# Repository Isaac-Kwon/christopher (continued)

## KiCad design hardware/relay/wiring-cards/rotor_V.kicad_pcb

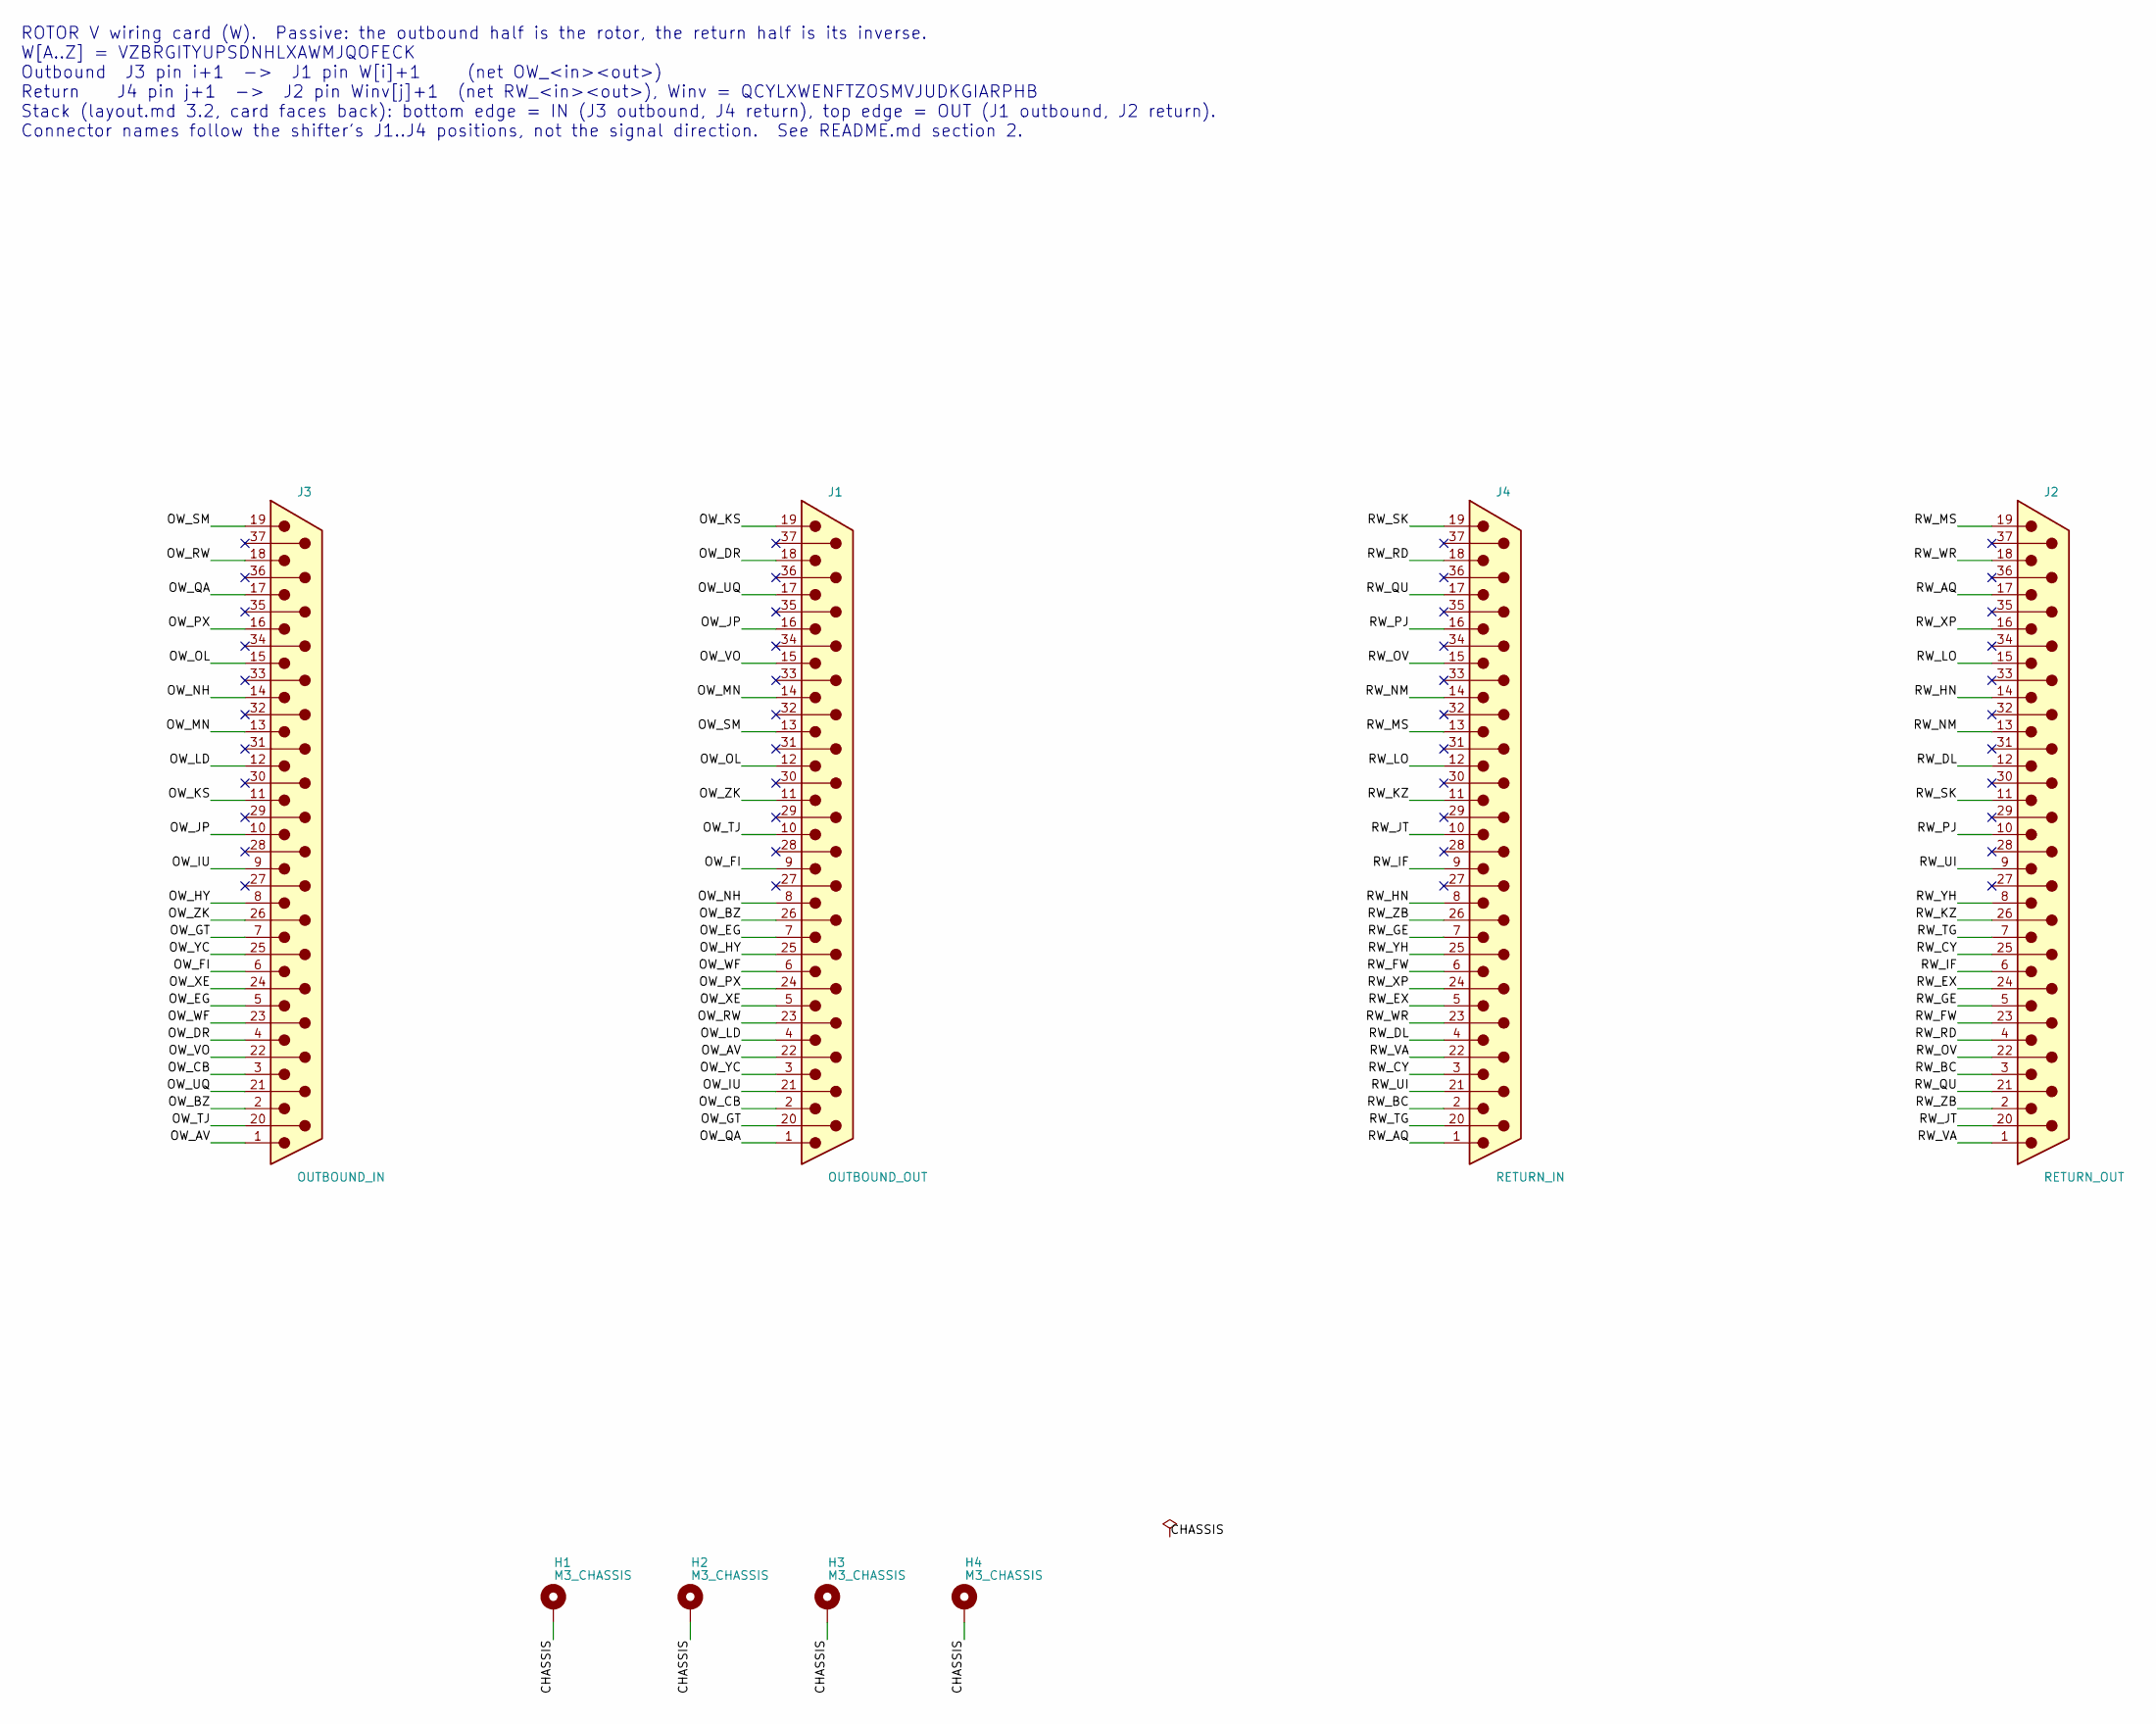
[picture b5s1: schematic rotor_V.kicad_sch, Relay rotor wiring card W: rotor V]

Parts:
H1, H2, H3, H4: M3_CHASSIS; MountingHole_3.2mm_M3_Pad
J1: OUTBOUND_OUT; DSUB-37_Pins_Horizontal_P2.77x2.84mm_EdgePinOffset9.90mm_Ho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
J2: RETURN_OUT; DSUB-37_Pins_Horizontal_P2.77x2.84mm_EdgePinOffset9.90mm_Ho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
J3: OUTBOUND_IN; DSUB-37_Pins_Horizontal_P2.77x2.84mm_EdgePinOffset9.90mm_Ho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
J4: RETURN_IN; DSUB-37_Pins_Horizontal_P2.77x2.84mm_EdgePinOffset9.90mm_Ho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

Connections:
/CHASSIS: H1.1, H2.1, H3.1, H4.1, J1.SH, J2.SH, J3.SH, J4.SH
/OW_AV: J1.22, J3.1
/OW_BZ: J1.26, J3.2
/OW_CB: J1.2, J3.3
/OW_DR: J1.18, J3.4
/OW_EG: J1.7, J3.5
/OW_FI: J1.9, J3.6
/OW_GT: J1.20, J3.7
/OW_HY: J1.25, J3.8
/OW_IU: J1.21, J3.9
/OW_JP: J1.16, J3.10
/OW_KS: J1.19, J3.11
/OW_LD: J1.4, J3.12
/OW_MN: J1.14, J3.13
/OW_NH: J1.8, J3.14
/OW_OL: J1.12, J3.15
/OW_PX: J1.24, J3.16
/OW_QA: J1.1, J3.17
/OW_RW: J1.23, J3.18
/OW_SM: J1.13, J3.19
/OW_TJ: J1.10, J3.20
/OW_UQ: J1.17, J3.21
/OW_VO: J1.15, J3.22
/OW_WF: J1.6, J3.23
/OW_XE: J1.5, J3.24
/OW_YC: J1.3, J3.25
/OW_ZK: J1.11, J3.26
/RW_AQ: J2.17, J4.1
/RW_BC: J2.3, J4.2
/RW_CY: J2.25, J4.3
/RW_DL: J2.12, J4.4
/RW_EX: J2.24, J4.5
/RW_FW: J2.23, J4.6
/RW_GE: J2.5, J4.7
/RW_HN: J2.14, J4.8
/RW_IF: J2.6, J4.9
/RW_JT: J2.20, J4.10
/RW_KZ: J2.26, J4.11
/RW_LO: J2.15, J4.12
/RW_MS: J2.19, J4.13
/RW_NM: J2.13, J4.14
/RW_OV: J2.22, J4.15
/RW_PJ: J2.10, J4.16
/RW_QU: J2.21, J4.17
/RW_RD: J2.4, J4.18
/RW_SK: J2.11, J4.19
/RW_TG: J2.7, J4.20
/RW_UI: J2.9, J4.21
/RW_VA: J2.1, J4.22
/RW_WR: J2.18, J4.23
/RW_XP: J2.16, J4.24
/RW_YH: J2.8, J4.25
/RW_ZB: J2.2, J4.26

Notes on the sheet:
ROTOR V wiring card (W). Passive: the outbound half is the rotor, the return half is its inverse. W[A..Z] = VZBRGITYUPSDNHLXAWMJQOFECK Outbound J3 pin i+1 -> J1 pin W[i]+1 (net OW_<in><out>) Return J4 pin j+1 -> J2 pin Winv[j]+1 (net RW_<in><out>), Winv = QCYLXWENFTZOSMVJUDKGIARPHB Stack (layout.md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

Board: 2 copper layers, 8 parts (0 on the bottom side), 53 nets, no tracks yet.

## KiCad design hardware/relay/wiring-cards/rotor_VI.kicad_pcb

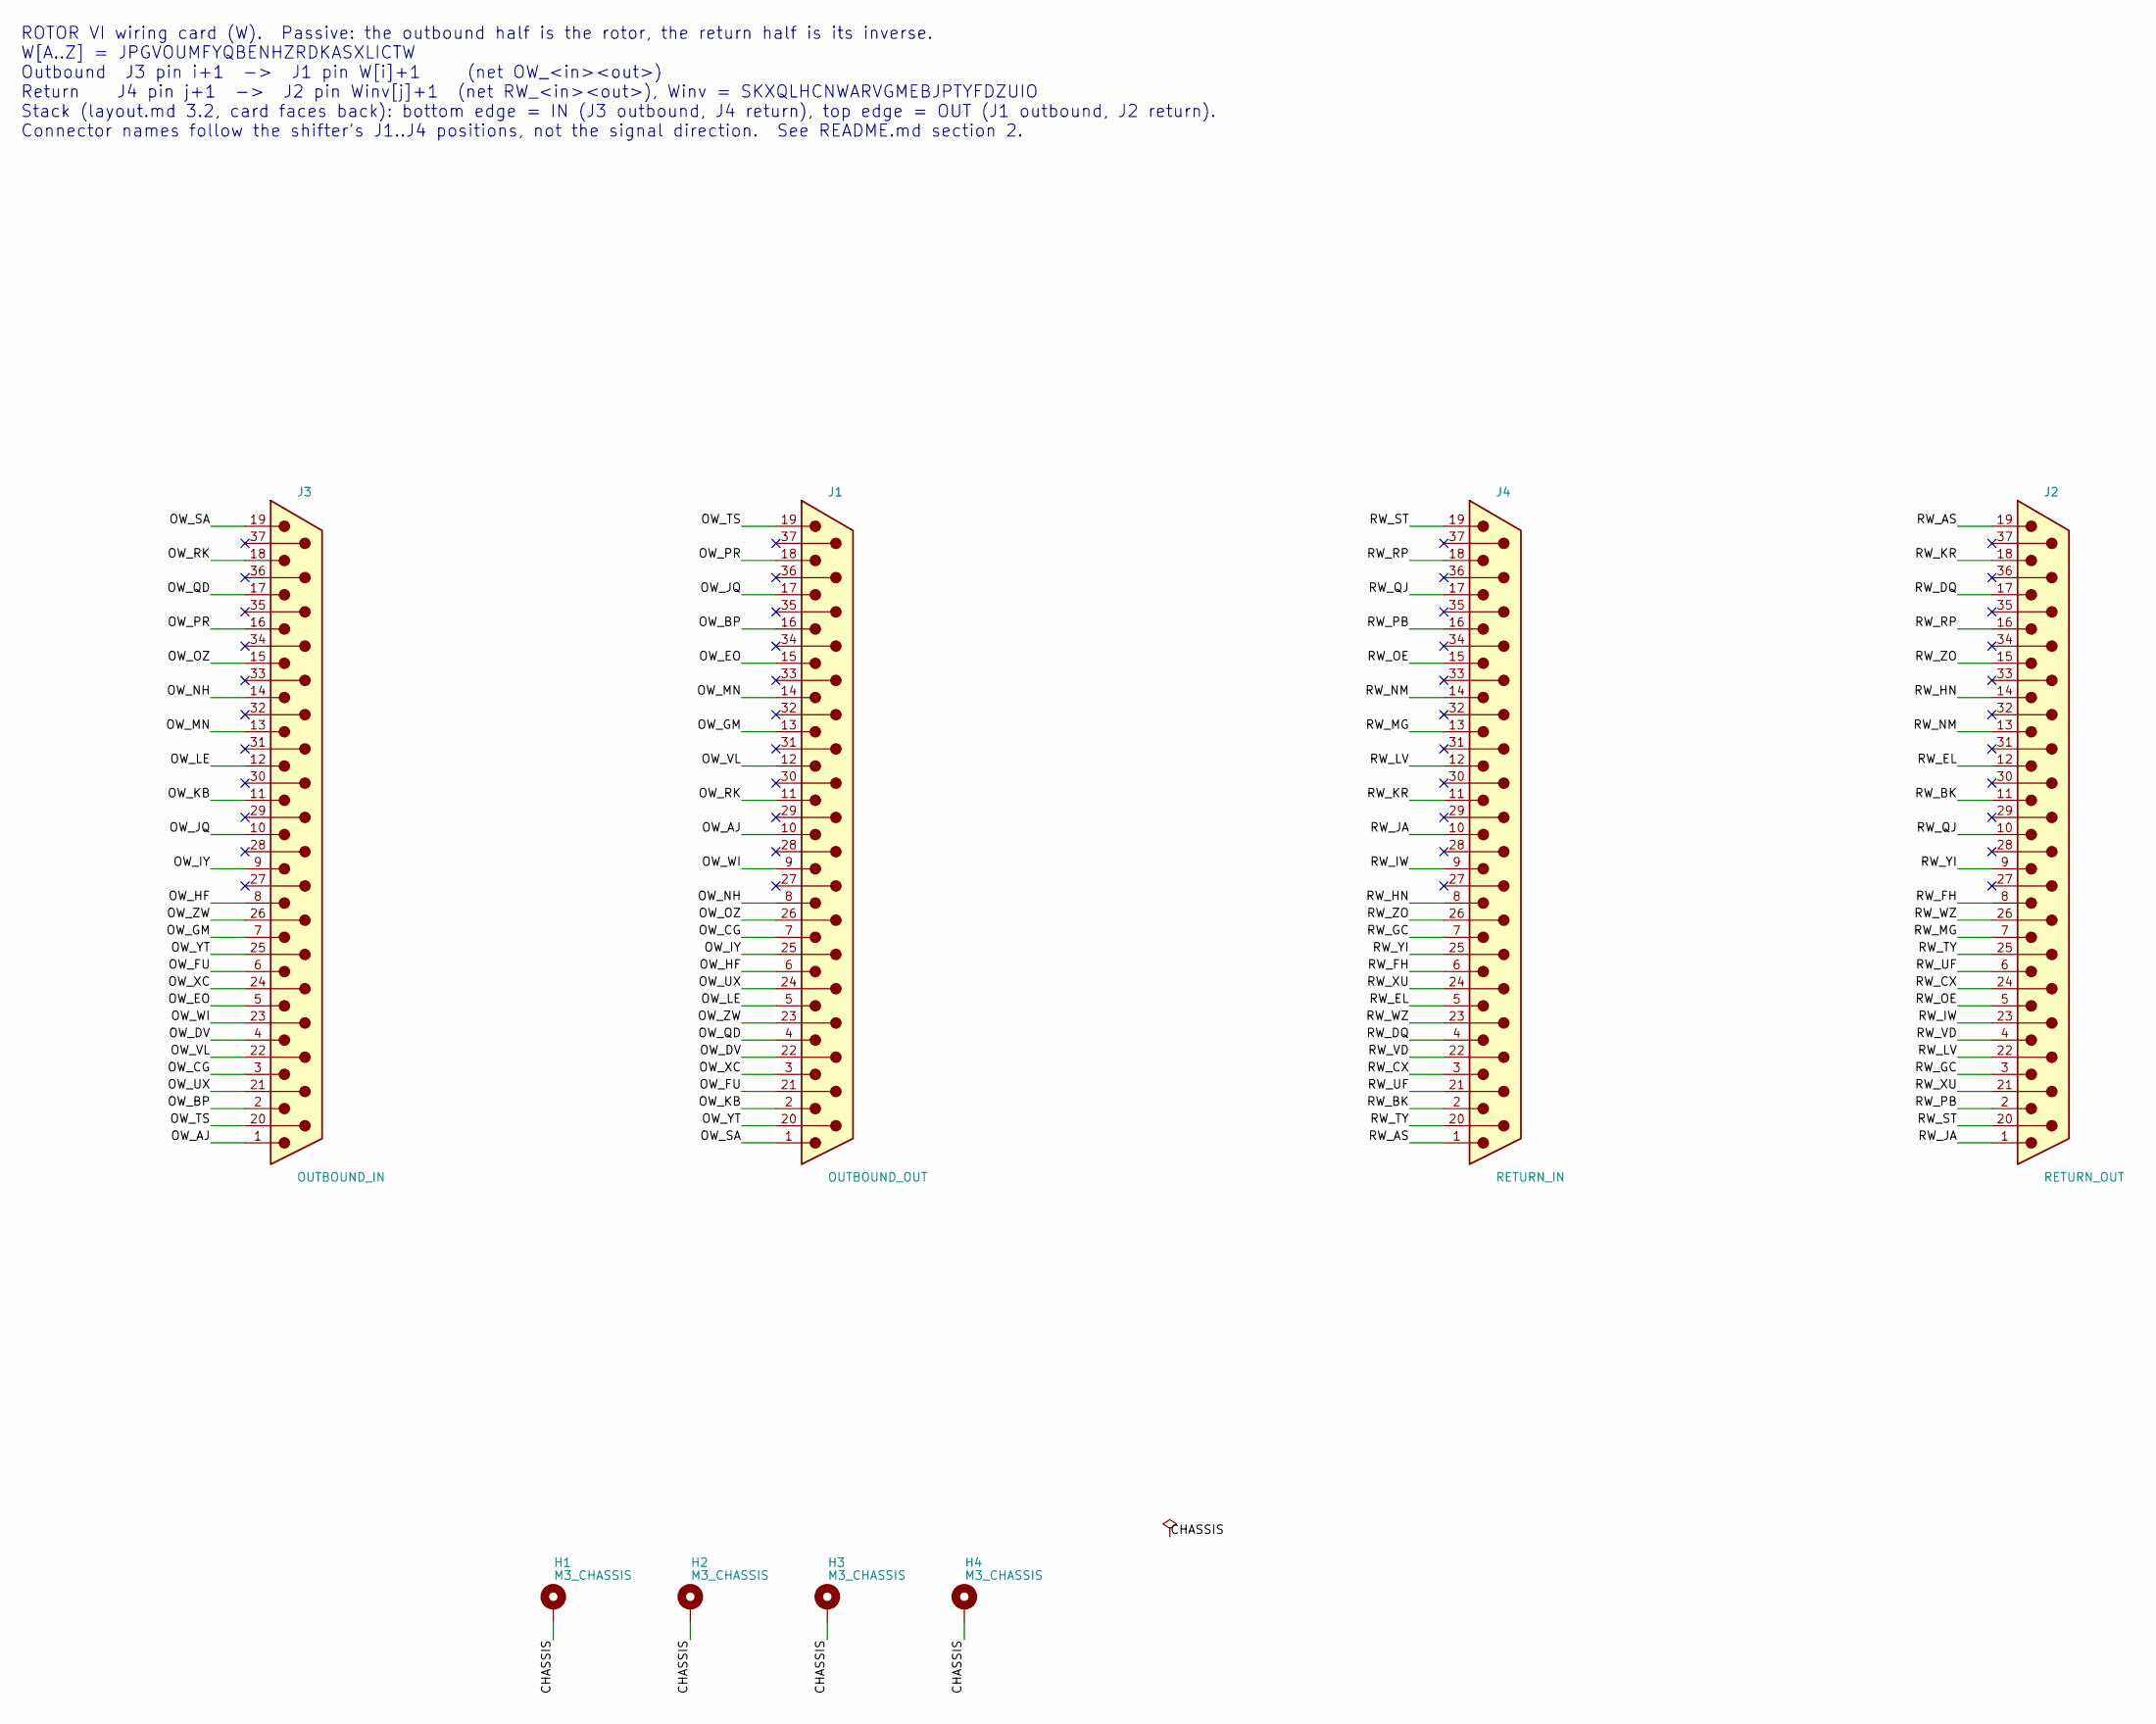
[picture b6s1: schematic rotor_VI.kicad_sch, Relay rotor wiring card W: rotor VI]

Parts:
H1, H2, H3, H4: M3_CHASSIS; MountingHole_3.2mm_M3_Pad
J1: OUTBOUND_OUT; DSUB-37_Pins_Horizontal_P2.77x2.84mm_EdgePinOffset9.90mm_Ho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
J2: RETURN_OUT; DSUB-37_Pins_Horizontal_P2.77x2.84mm_EdgePinOffset9.90mm_Ho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
J3: OUTBOUND_IN; DSUB-37_Pins_Horizontal_P2.77x2.84mm_EdgePinOffset9.90mm_Ho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
J4: RETURN_IN; DSUB-37_Pins_Horizontal_P2.77x2.84mm_EdgePinOffset9.90mm_Ho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

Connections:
/CHASSIS: H1.1, H2.1, H3.1, H4.1, J1.SH, J2.SH, J3.SH, J4.SH
/OW_AJ: J1.10, J3.1
/OW_BP: J1.16, J3.2
/OW_CG: J1.7, J3.3
/OW_DV: J1.22, J3.4
/OW_EO: J1.15, J3.5
/OW_FU: J1.21, J3.6
/OW_GM: J1.13, J3.7
/OW_HF: J1.6, J3.8
/OW_IY: J1.25, J3.9
/OW_JQ: J1.17, J3.10
/OW_KB: J1.2, J3.11
/OW_LE: J1.5, J3.12
/OW_MN: J1.14, J3.13
/OW_NH: J1.8, J3.14
/OW_OZ: J1.26, J3.15
/OW_PR: J1.18, J3.16
/OW_QD: J1.4, J3.17
/OW_RK: J1.11, J3.18
/OW_SA: J1.1, J3.19
/OW_TS: J1.19, J3.20
/OW_UX: J1.24, J3.21
/OW_VL: J1.12, J3.22
/OW_WI: J1.9, J3.23
/OW_XC: J1.3, J3.24
/OW_YT: J1.20, J3.25
/OW_ZW: J1.23, J3.26
/RW_AS: J2.19, J4.1
/RW_BK: J2.11, J4.2
/RW_CX: J2.24, J4.3
/RW_DQ: J2.17, J4.4
/RW_EL: J2.12, J4.5
/RW_FH: J2.8, J4.6
/RW_GC: J2.3, J4.7
/RW_HN: J2.14, J4.8
/RW_IW: J2.23, J4.9
/RW_JA: J2.1, J4.10
/RW_KR: J2.18, J4.11
/RW_LV: J2.22, J4.12
/RW_MG: J2.7, J4.13
/RW_NM: J2.13, J4.14
/RW_OE: J2.5, J4.15
/RW_PB: J2.2, J4.16
/RW_QJ: J2.10, J4.17
/RW_RP: J2.16, J4.18
/RW_ST: J2.20, J4.19
/RW_TY: J2.25, J4.20
/RW_UF: J2.6, J4.21
/RW_VD: J2.4, J4.22
/RW_WZ: J2.26, J4.23
/RW_XU: J2.21, J4.24
/RW_YI: J2.9, J4.25
/RW_ZO: J2.15, J4.26

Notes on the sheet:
ROTOR VI wiring card (W). Passive: the outbound half is the rotor, the return half is its inverse. W[A..Z] = JPGVOUMFYQBENHZRDKASXLICTW Outbound J3 pin i+1 -> J1 pin W[i]+1 (net OW_<in><out>) Return J4 pin j+1 -> J2 pin Winv[j]+1 (net RW_<in><out>), Winv = SKXQLHCNWARVGMEBJPTYFDZUIO Stack (layout.m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

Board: 2 copper layers, 8 parts (0 on the bottom side), 53 nets, no tracks yet.

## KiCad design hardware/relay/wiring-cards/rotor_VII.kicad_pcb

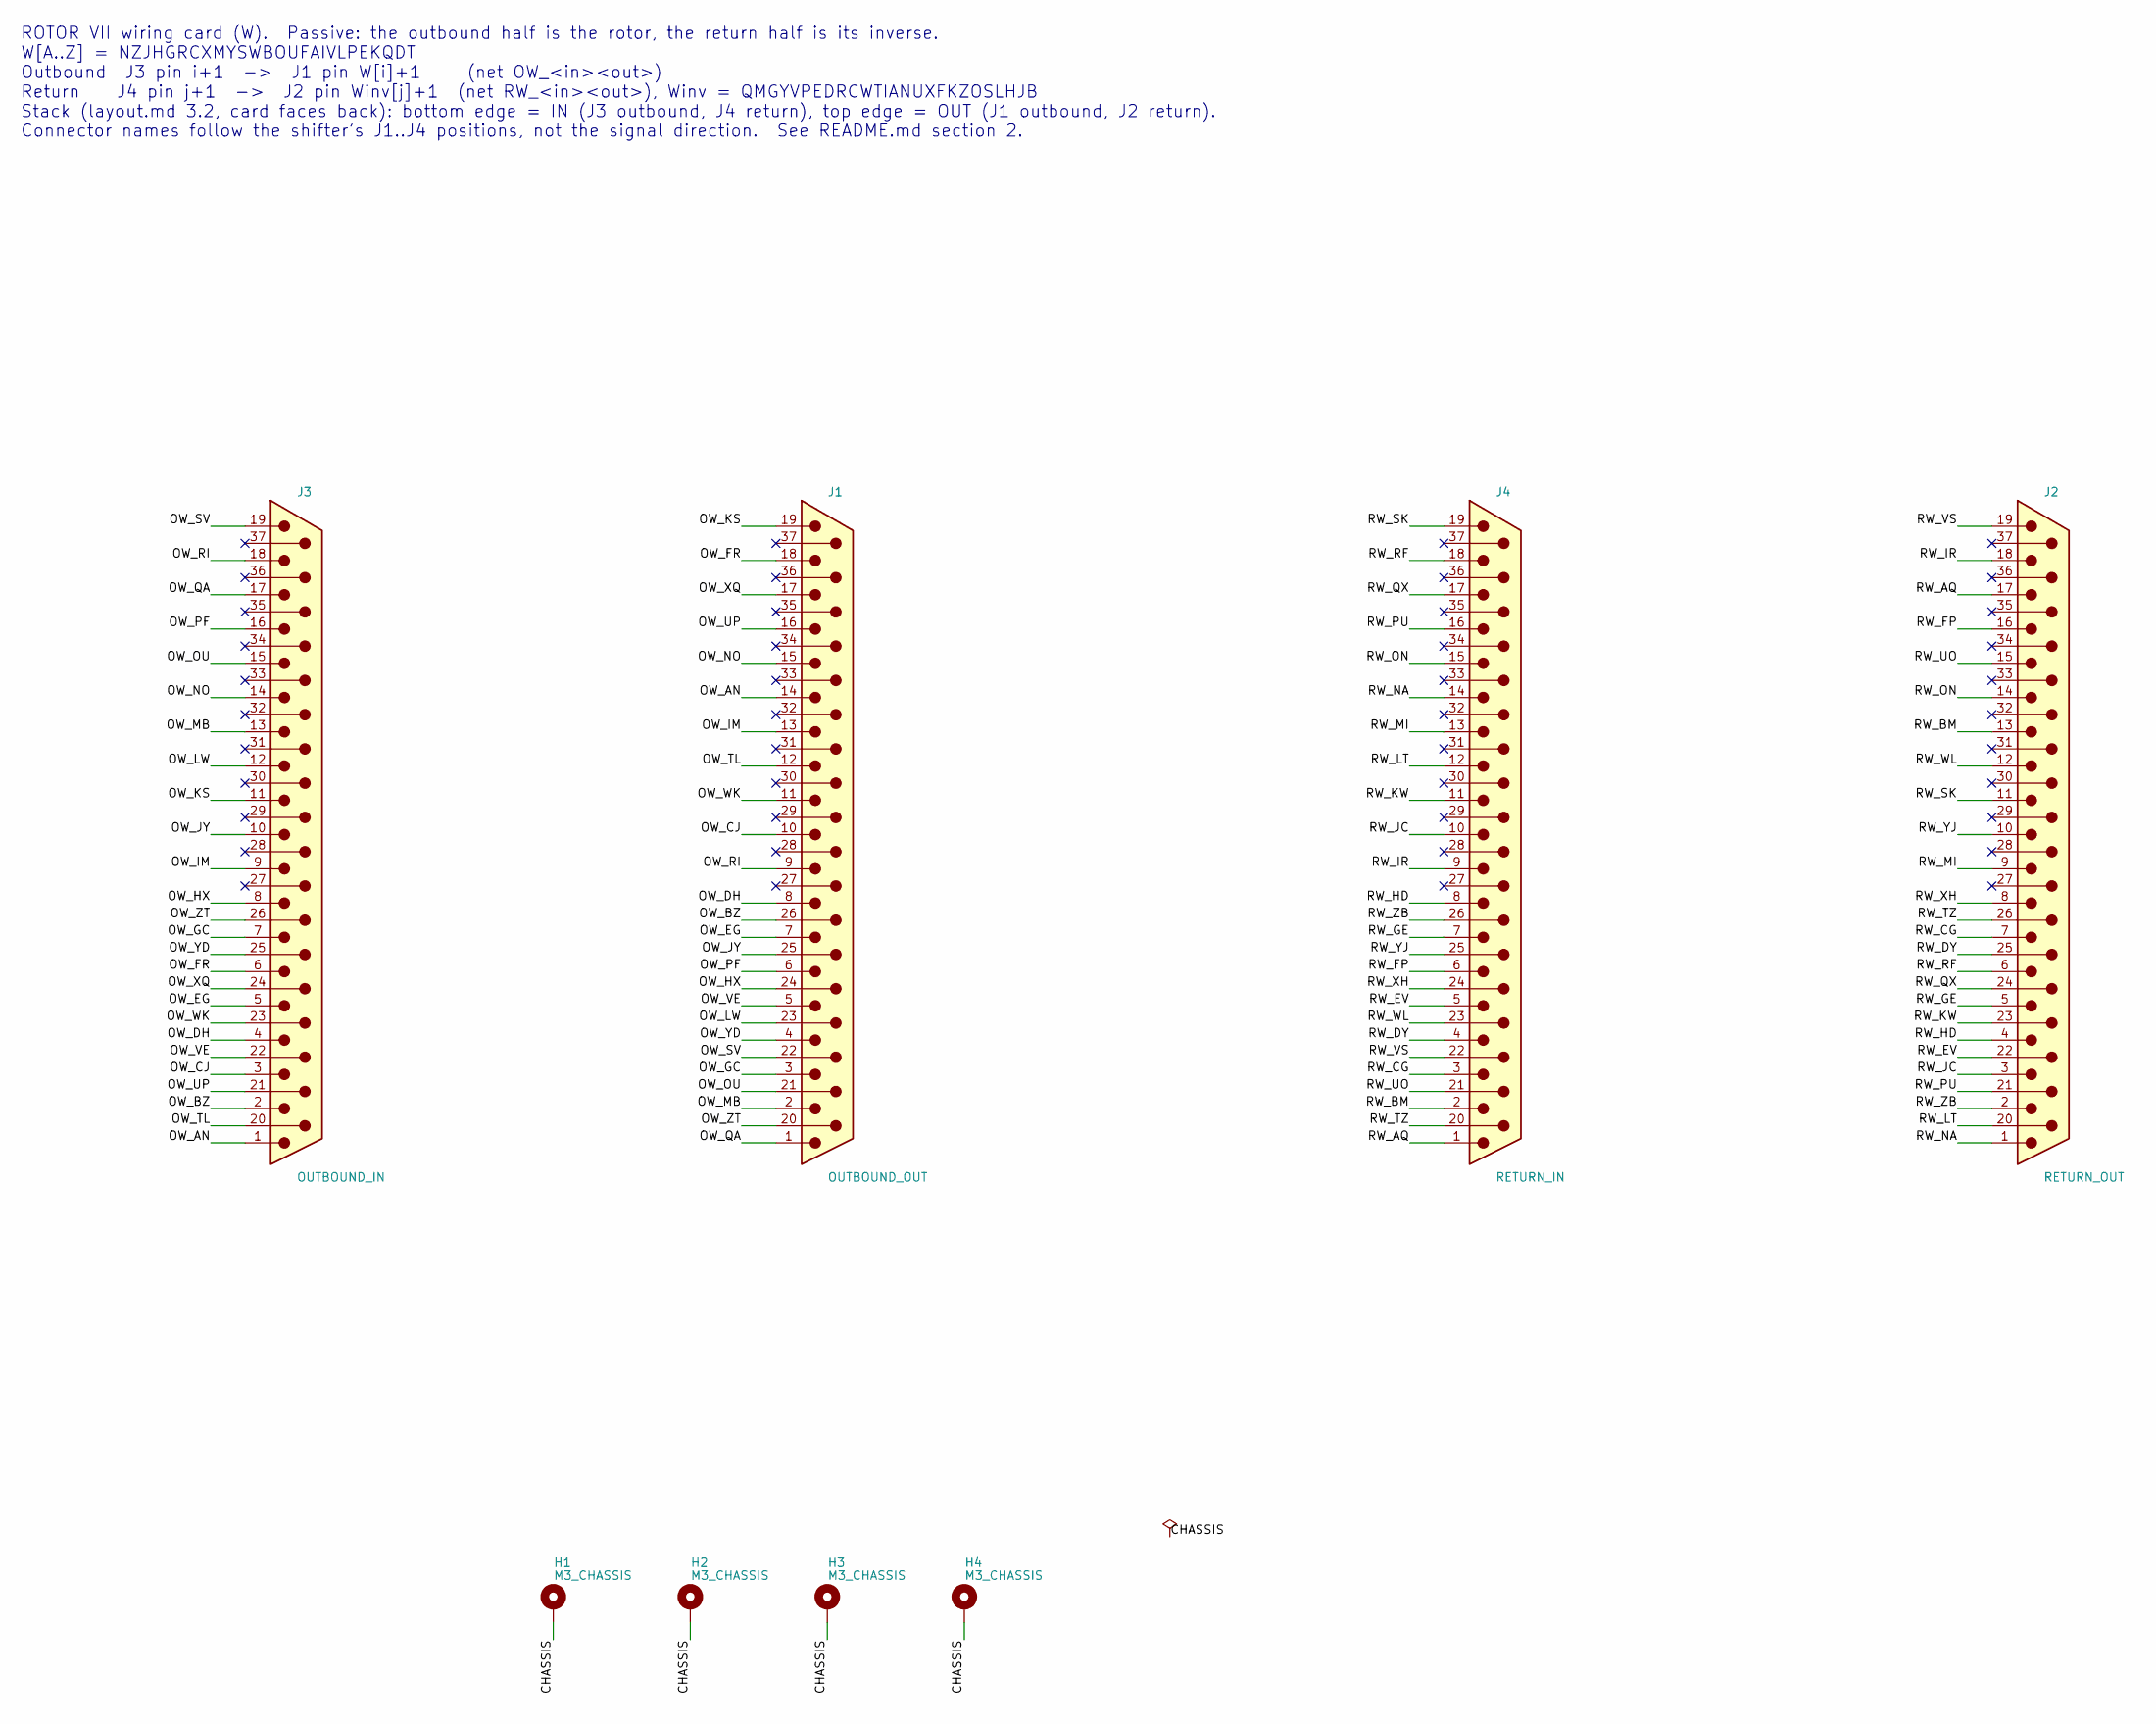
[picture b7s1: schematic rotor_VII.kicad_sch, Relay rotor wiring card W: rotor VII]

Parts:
H1, H2, H3, H4: M3_CHASSIS; MountingHole_3.2mm_M3_Pad
J1: OUTBOUND_OUT; DSUB-37_Pins_Horizontal_P2.77x2.84mm_EdgePinOffset9.90mm_Ho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
J2: RETURN_OUT; DSUB-37_Pins_Horizontal_P2.77x2.84mm_EdgePinOffset9.90mm_Ho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
J3: OUTBOUND_IN; DSUB-37_Pins_Horizontal_P2.77x2.84mm_EdgePinOffset9.90mm_Ho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
J4: RETURN_IN; DSUB-37_Pins_Horizontal_P2.77x2.84mm_EdgePinOffset9.90mm_Ho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

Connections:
/CHASSIS: H1.1, H2.1, H3.1, H4.1, J1.SH, J2.SH, J3.SH, J4.SH
/OW_AN: J1.14, J3.1
/OW_BZ: J1.26, J3.2
/OW_CJ: J1.10, J3.3
/OW_DH: J1.8, J3.4
/OW_EG: J1.7, J3.5
/OW_FR: J1.18, J3.6
/OW_GC: J1.3, J3.7
/OW_HX: J1.24, J3.8
/OW_IM: J1.13, J3.9
/OW_JY: J1.25, J3.10
/OW_KS: J1.19, J3.11
/OW_LW: J1.23, J3.12
/OW_MB: J1.2, J3.13
/OW_NO: J1.15, J3.14
/OW_OU: J1.21, J3.15
/OW_PF: J1.6, J3.16
/OW_QA: J1.1, J3.17
/OW_RI: J1.9, J3.18
/OW_SV: J1.22, J3.19
/OW_TL: J1.12, J3.20
/OW_UP: J1.16, J3.21
/OW_VE: J1.5, J3.22
/OW_WK: J1.11, J3.23
/OW_XQ: J1.17, J3.24
/OW_YD: J1.4, J3.25
/OW_ZT: J1.20, J3.26
/RW_AQ: J2.17, J4.1
/RW_BM: J2.13, J4.2
/RW_CG: J2.7, J4.3
/RW_DY: J2.25, J4.4
/RW_EV: J2.22, J4.5
/RW_FP: J2.16, J4.6
/RW_GE: J2.5, J4.7
/RW_HD: J2.4, J4.8
/RW_IR: J2.18, J4.9
/RW_JC: J2.3, J4.10
/RW_KW: J2.23, J4.11
/RW_LT: J2.20, J4.12
/RW_MI: J2.9, J4.13
/RW_NA: J2.1, J4.14
/RW_ON: J2.14, J4.15
/RW_PU: J2.21, J4.16
/RW_QX: J2.24, J4.17
/RW_RF: J2.6, J4.18
/RW_SK: J2.11, J4.19
/RW_TZ: J2.26, J4.20
/RW_UO: J2.15, J4.21
/RW_VS: J2.19, J4.22
/RW_WL: J2.12, J4.23
/RW_XH: J2.8, J4.24
/RW_YJ: J2.10, J4.25
/RW_ZB: J2.2, J4.26

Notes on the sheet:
ROTOR VII wiring card (W). Passive: the outbound half is the rotor, the return half is its inverse. W[A..Z] = NZJHGRCXMYSWBOUFAIVLPEKQDT Outbound J3 pin i+1 -> J1 pin W[i]+1 (net OW_<in><out>) Return J4 pin j+1 -> J2 pin Winv[j]+1 (net RW_<in><out>), Winv = QMGYVPEDRCWTIANUXFKZOSLHJB Stack (layout.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

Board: 2 copper layers, 8 parts (0 on the bottom side), 53 nets, no tracks yet.

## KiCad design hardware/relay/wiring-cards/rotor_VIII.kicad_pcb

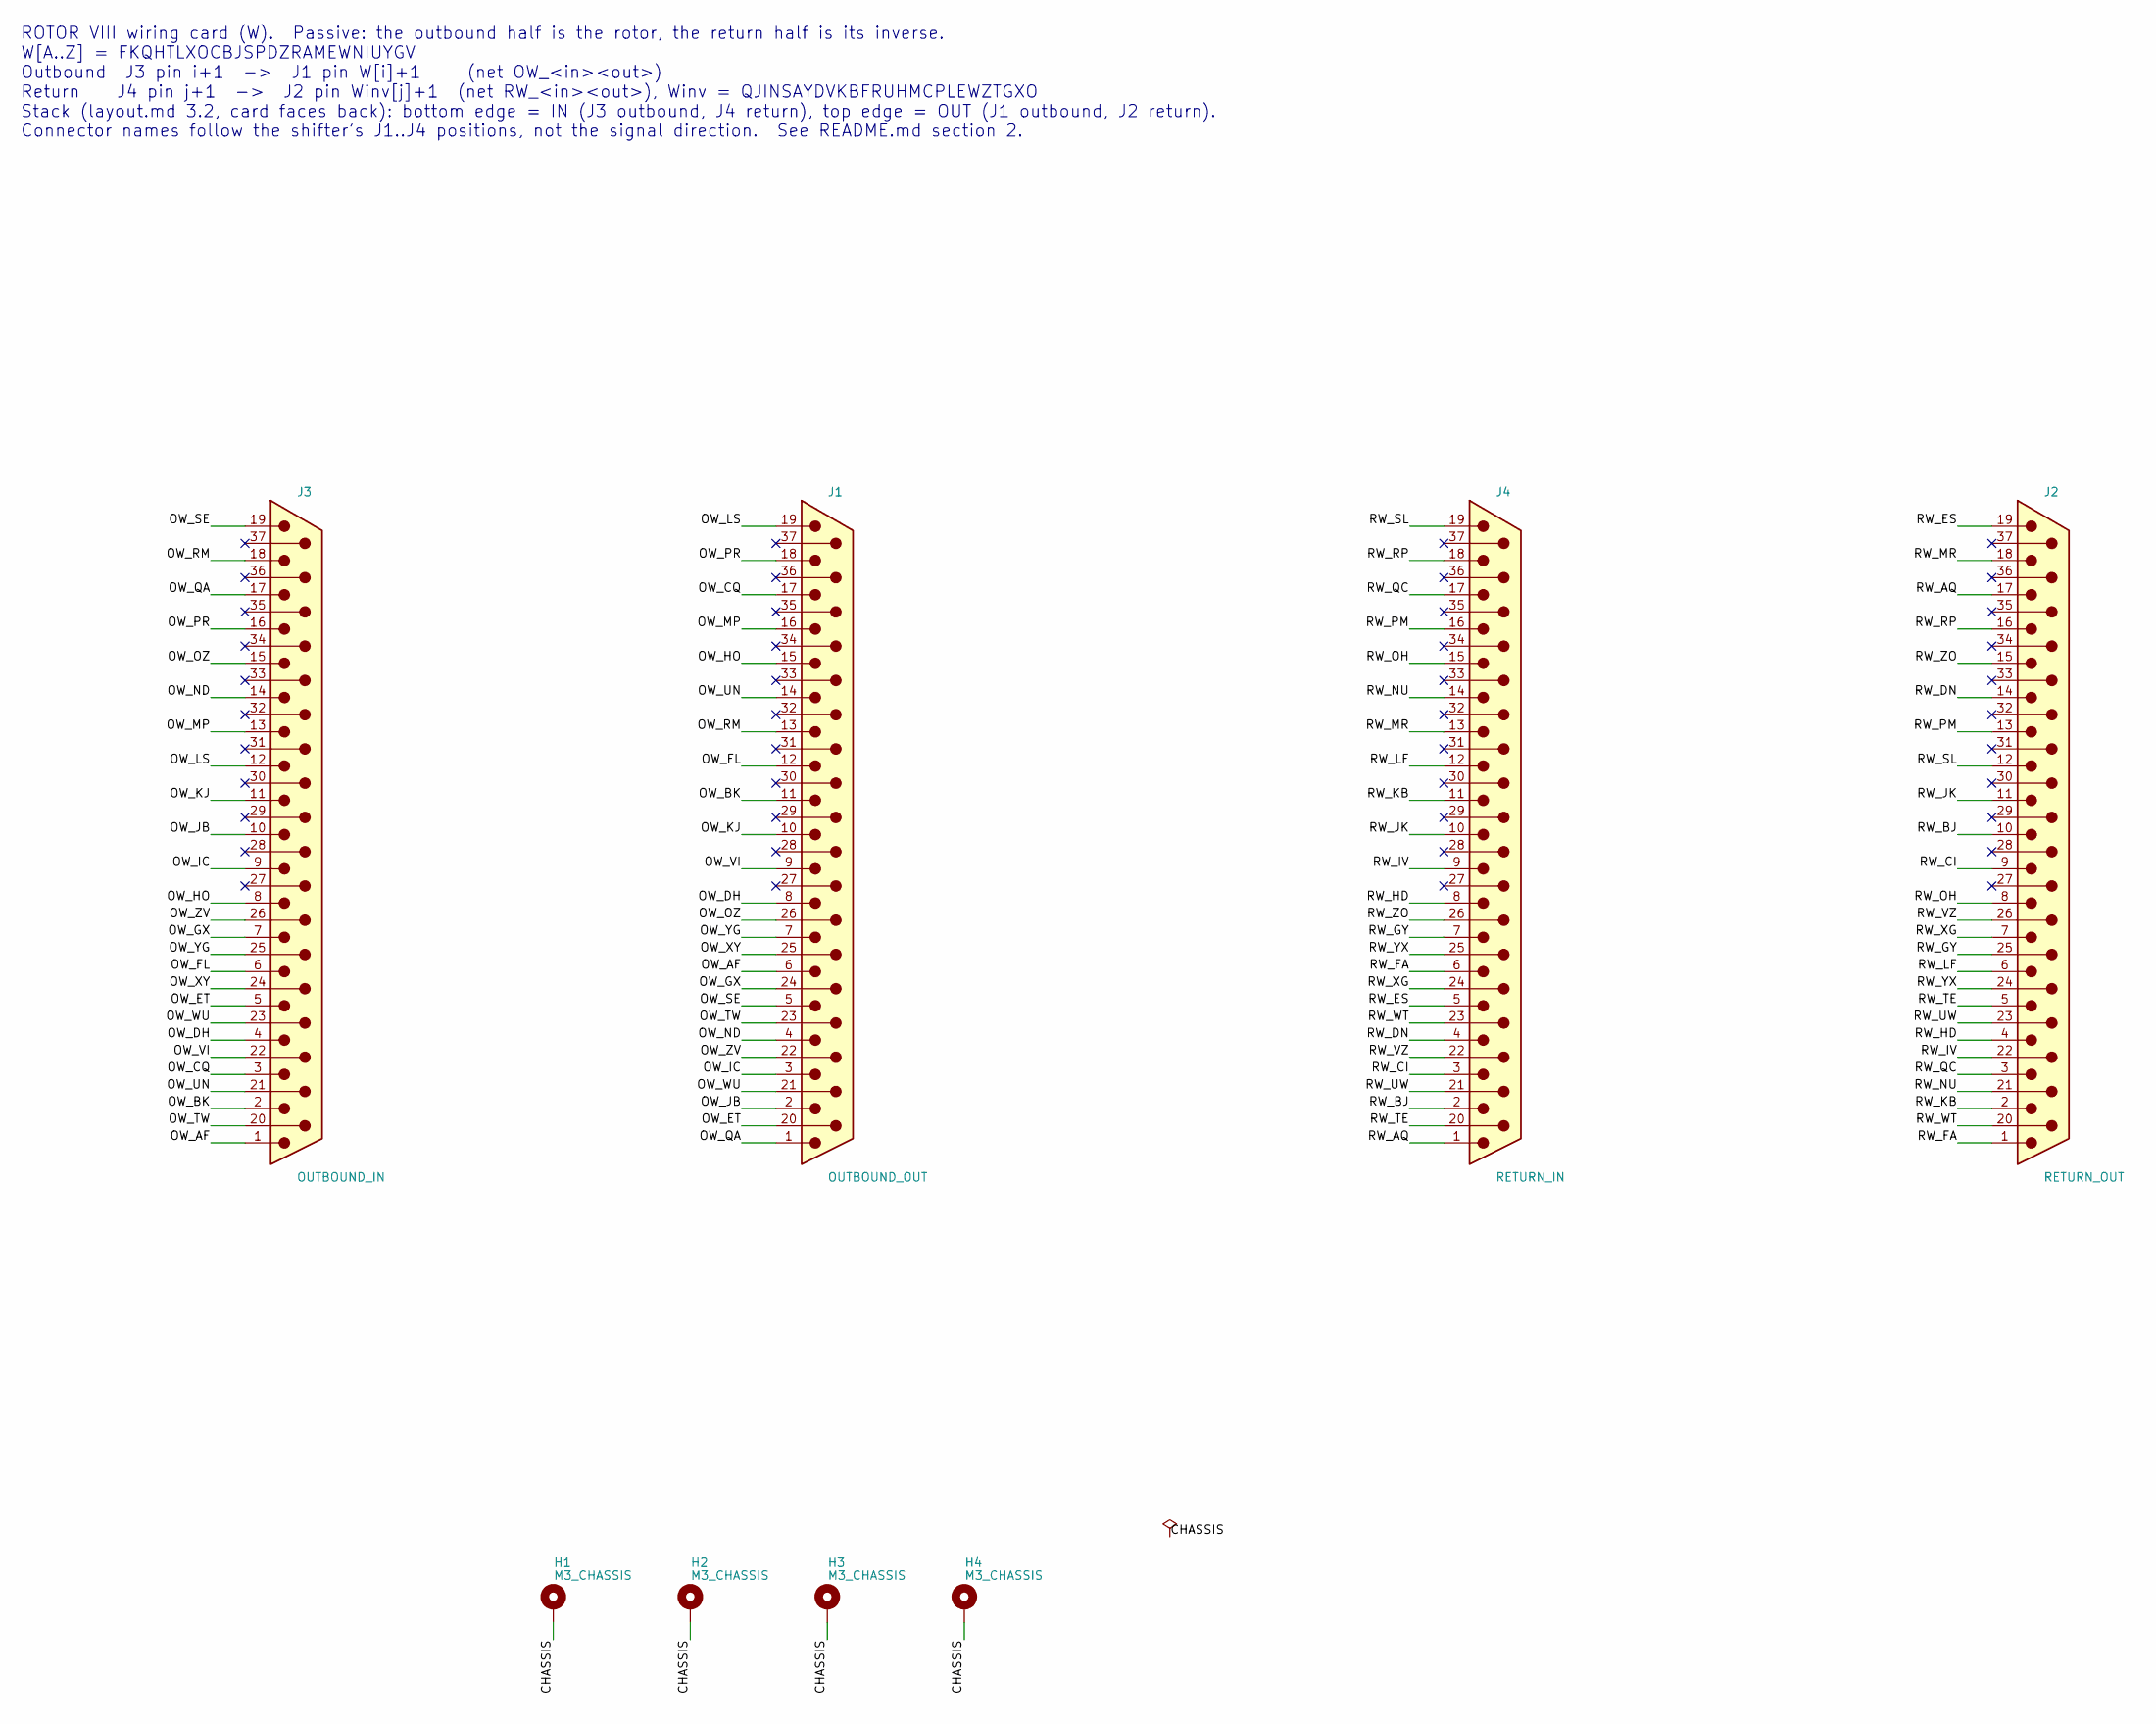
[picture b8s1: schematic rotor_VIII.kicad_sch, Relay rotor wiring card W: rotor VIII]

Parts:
H1, H2, H3, H4: M3_CHASSIS; MountingHole_3.2mm_M3_Pad
J1: OUTBOUND_OUT; DSUB-37_Pins_Horizontal_P2.77x2.84mm_EdgePinOffset9.90mm_Ho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
J2: RETURN_OUT; DSUB-37_Pins_Horizontal_P2.77x2.84mm_EdgePinOffset9.90mm_Ho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
J3: OUTBOUND_IN; DSUB-37_Pins_Horizontal_P2.77x2.84mm_EdgePinOffset9.90mm_Ho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
J4: RETURN_IN; DSUB-37_Pins_Horizontal_P2.77x2.84mm_EdgePinOffset9.90mm_Ho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

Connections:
/CHASSIS: H1.1, H2.1, H3.1, H4.1, J1.SH, J2.SH, J3.SH, J4.SH
/OW_AF: J1.6, J3.1
/OW_BK: J1.11, J3.2
/OW_CQ: J1.17, J3.3
/OW_DH: J1.8, J3.4
/OW_ET: J1.20, J3.5
/OW_FL: J1.12, J3.6
/OW_GX: J1.24, J3.7
/OW_HO: J1.15, J3.8
/OW_IC: J1.3, J3.9
/OW_JB: J1.2, J3.10
/OW_KJ: J1.10, J3.11
/OW_LS: J1.19, J3.12
/OW_MP: J1.16, J3.13
/OW_ND: J1.4, J3.14
/OW_OZ: J1.26, J3.15
/OW_PR: J1.18, J3.16
/OW_QA: J1.1, J3.17
/OW_RM: J1.13, J3.18
/OW_SE: J1.5, J3.19
/OW_TW: J1.23, J3.20
/OW_UN: J1.14, J3.21
/OW_VI: J1.9, J3.22
/OW_WU: J1.21, J3.23
/OW_XY: J1.25, J3.24
/OW_YG: J1.7, J3.25
/OW_ZV: J1.22, J3.26
/RW_AQ: J2.17, J4.1
/RW_BJ: J2.10, J4.2
/RW_CI: J2.9, J4.3
/RW_DN: J2.14, J4.4
/RW_ES: J2.19, J4.5
/RW_FA: J2.1, J4.6
/RW_GY: J2.25, J4.7
/RW_HD: J2.4, J4.8
/RW_IV: J2.22, J4.9
/RW_JK: J2.11, J4.10
/RW_KB: J2.2, J4.11
/RW_LF: J2.6, J4.12
/RW_MR: J2.18, J4.13
/RW_NU: J2.21, J4.14
/RW_OH: J2.8, J4.15
/RW_PM: J2.13, J4.16
/RW_QC: J2.3, J4.17
/RW_RP: J2.16, J4.18
/RW_SL: J2.12, J4.19
/RW_TE: J2.5, J4.20
/RW_UW: J2.23, J4.21
/RW_VZ: J2.26, J4.22
/RW_WT: J2.20, J4.23
/RW_XG: J2.7, J4.24
/RW_YX: J2.24, J4.25
/RW_ZO: J2.15, J4.26

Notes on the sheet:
ROTOR VIII wiring card (W). Passive: the outbound half is the rotor, the return half is its inverse. W[A..Z] = FKQHTLXOCBJSPDZRAMEWNIUYGV Outbound J3 pin i+1 -> J1 pin W[i]+1 (net OW_<in><out>) Return J4 pin j+1 -> J2 pin Winv[j]+1 (net RW_<in><out>), Winv = QJINSAYDVKBFRUHMCPLEWZTGXO Stack (layout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

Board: 2 copper layers, 8 parts (0 on the bottom side), 53 nets, no tracks yet.
